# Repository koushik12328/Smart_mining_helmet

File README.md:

# Smart Mining Helmet for Real Time Hazard Detection
**Developed by:** Ch Koushik | MGIT ECE

---

## 1. Aim
To design and develop a decentralized, infrastructure-less safety system for underground mining that utilizes **Machine-to-Machine (M2M)** communication to provide real-time environmental monitoring and instant hazard alerts without relying on Wi-Fi or cellular networks.

## 2. Abstract
Underground mining environments present a unique challenge for safety communication due to signal attenuation through rock strata and the high cost of network infrastructure. This project proposes a **Smart Mining Helmet** that functions as an autonomous node. By leveraging the **ESP-NOW** protocol, the helmet (Transmitter) communicates directly with a base station (Receiver) via hardware MAC addresses. 

The system integrates a multi-sensor array—including Methane (MQ-4), smoke (MQ-2), air quality (MQ-135), and environmental sensors (DHT11, BMP180)—to monitor for life-threatening conditions. Hardware design was executed in **KiCad** for optimized signal integrity, while the software architecture employs a non-blocking state machine with digital filtering to ensure data reliability. Results demonstrate ultra-low latency (<10ms) and robust connectivity, proving the system's efficacy for real-time industrial safety applications.

---

## 3. Components Required

### A. Smart Helmet (Transmitter Module)
* **ESP32 DevKit V1:** Core microcontroller utilizing the ESP-NOW protocol for data broadcast.
* **MQ-4 Sensor:** Dedicated for Methane (CH4) gas detection.
* **MQ-2 Sensor:** Detects Smoke, LPG, and Carbon Monoxide.
* **MQ-135 Sensor:** Monitors general Air Quality (NH3, Benzene, etc.).
* **DHT11:** Provides Temperature and Humidity data.
* **BMP180:** High-precision sensor for Barometric Pressure and Altitude monitoring.
* **Status LEDs:** Local indicators for power and transmission verification.
* **Custom Transmitter PCB:** Designed in KiCad with a compact form factor for helmet mounting.

### B. Base Station / Node (Receiver Module)
* **ESP32 DevKit V1:** Configured to listen for specific MAC addresses and process incoming data packets.
* **16x2 LCD with I2C Module:** Displays real-time sensor telemetry from the helmet.
* **Active Buzzer (5V):** Sounds a high-decibel alarm when sensor thresholds are breached.
* **Visual Alarm LED:** High-intensity LED for immediate hazard recognition.
* **Custom Receiver PCB:** Designed in KiCad with an integrated I2C header and centralized power distribution.

---

## 4. Procedure

### A. Hardware Analysis
The hardware design focuses on **Signal Integrity** and **Power Management**. 
* **Sensing Layer:** The gas sensors (MQ series) are analog; their output is fed into the ESP32’s 12-bit ADC. I implemented a common ground plane in KiCad to reduce noise during high-frequency Wi-Fi bursts.
* **PCB Strategy:** The Transmitter PCB is designed for a compact footprint to fit the helmet. The Receiver PCB utilizes the **I2C protocol** via the PCF8574 expander, which allowed me to reduce the LCD wiring from 10+ pins down to just 2 (SDA/SCL), simplifying the routing significantly.
* **Power Logic:** Because the MQ sensors have internal heaters that pull high current (~800mA peak), I ensured the power traces on the PCB were wide enough to prevent voltage drops that could crash the ESP32.

### B. Software Analysis
The software is the "intelligence" of the system, acting as a non-blocking state machine.
* **M2M Protocol (ESP-NOW):** Unlike standard Wi-Fi, the firmware bypasses the router. I hardcoded the Receiver's hardware MAC address into the Transmitter’s peer list. This allows for near-instant "Power-On-to-Data" transmission.
* **Data Structuring:** I defined a custom `struct` to package sensor values. This ensures that the Receiver interprets the incoming raw bytes correctly every time.
* **Signal Processing:** To handle the inherent "jitter" of analog gas sensors, I implemented a **Moving Average Filter** in the C++ code. This smooths out the readings before they are sent over the air.
* **Callback & ACK:** The software uses the `OnDataSent` callback. If the Receiver is out of range, the code detects the lack of an Acknowledgement (ACK) and triggers a "Link Fail" state without stopping the sensor polling loop.

---

## 5. Implementation
1. **PCB Fabrication:** The KiCad layouts were exported to Gerbers for fabrication.
2. **Firmware Upload:** The TX module was flashed with the sensor-gathering and ESP-NOW broadcast code. The RX module was flashed with the display and alert logic.
3. **M2M Pairing:** MAC addresses were verified and hardcoded for a dedicated point-to-point link.

---

## 6. Observations
* **Latency:** The "Sensor-to-Alert" delay was measured at approximately **10ms**, significantly faster than any Cloud-based IoT setup.
* **I2C Efficiency:** The I2C bus remained stable at 100kHz, providing clean data updates to the LCD every 500ms.
* **Range:** The ESP-NOW link remained robust even through moderate industrial interference, reaching up to 50 meters in non-line-of-sight conditions.

---

## 7. Results
* **Successful M2M Link:** Established a permanent MAC-to-MAC connection that requires zero external network infrastructure.
* **Hazard Response:** The system successfully triggered the buzzer within milliseconds of exposing the MQ-4 sensor to a methane-simulated environment.
* **Data Accuracy:** The moving average filter effectively removed ADC noise, providing stable, reliable PPM readings on the LCD.

---

## 8. Conclusion
The project proves that for high-risk environments like mines, **Machine-to-Machine (M2M)** communication is far superior to standard IoT. By combining custom KiCad hardware with a lean, non-blocking software stack, I created a safety system that is faster, more reliable, and completely independent of the internet.

---
*Department of Electronics and Communication Engineering | MGIT, Hyderabad*

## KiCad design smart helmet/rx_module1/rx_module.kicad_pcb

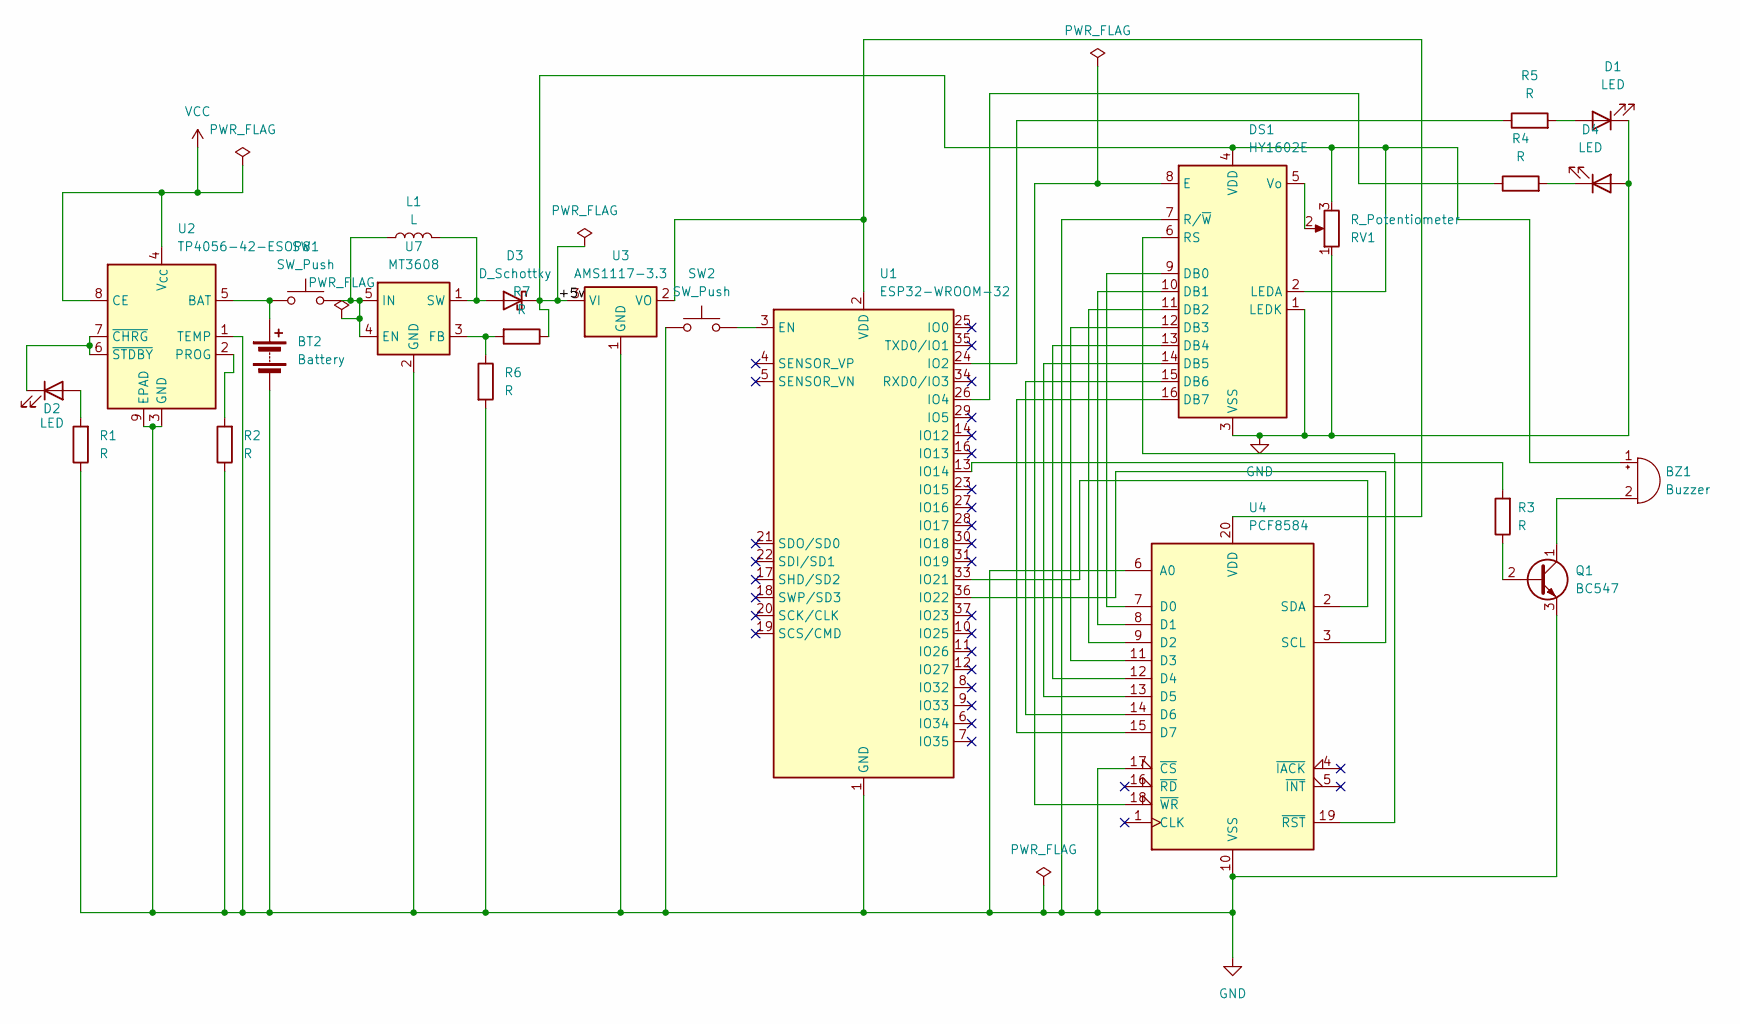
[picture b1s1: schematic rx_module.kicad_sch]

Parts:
BT2: Battery; JST_PH_S2B-PH-K_1x02_P2.00mm_Horizontal
BZ1: Buzzer; Buzzer_12x9.5RM7.6
D1, D2, D4: LED; LED_D5.0mm
D3: D_Schottky; D_SMA
DS1: HY1602E
L1: L; L_Radial_D7.8mm_P5.00mm_Fastron_07HCP
Q1: BC547; TO-92_Inline
R1, R2, R3, R4, R5, R6, R7: R; R_Axial_DIN0207_L6.3mm_D2.5mm_P7.62mm_Horizontal
RV1: R_Potentiometer; Potentiometer_Bourns_3386P_Vertical
SW1, SW2: SW_Push; SW_PUSH_6mm
U1: ESP32-WROOM-32
U2: TP4056-42-ESOP8; SOIC-8-1EP_3.9x4.9mm_P1.27mm_EP2.41x3.3mm_ThermalVias
U3: AMS1117-3.3; SOT-223-3_TabPin2
U4: PCF8584; DIP-20_W7.62mm
U7: MT3608; SOT-23-6

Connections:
/+5v: BZ1.1 (+), D3.1 (K), DS1.2 (LEDA), DS1.4 (VDD), R7.1, RV1.3, U3.3 (VI); also elsewhere on the board
GND: BT2.2 (-), D1.1 (K), D4.2 (A), DS1.1 (LEDK), DS1.3 (VSS), DS1.7 (R/~W), Q1.3 (E), R1.1, R2.1, R6.2, RV1.1, SW2.1, U1.1 (GND), U1.15 (GND), U1.38 (GND), U1.39 (GND), U2.1 (TEMP), U2.3 (GND), U2.9 (EPAD), U3.1 (GND), U4.6 (A0), U4.10 (VSS), U4.17 (~CS), U7.2 (GND); also elsewhere on the board
unnamed: BT2.1 (+), SW1.1, U2.5 (BAT)
unnamed: BZ1.2 (-), Q1.1 (C)
unnamed: D1.2 (A), R5.2
unnamed: D2.2 (A), R1.2
unnamed: D2.1 (K), U2.6 (~STDBY), U2.7 (~CHRG)
unnamed: D3.2 (A), L1.2, U7.1 (SW)
unnamed: D4.1 (K), R4.2
unnamed: DS1.9 (DB0), U4.7 (D0)
unnamed: DS1.10 (DB1), U4.8 (D1)
unnamed: DS1.11 (DB2), U4.9 (D2)
unnamed: DS1.12 (DB3), U4.11 (D3)
unnamed: DS1.13 (DB4), U4.12 (D4)
unnamed: DS1.14 (DB5), U4.13 (D5)
unnamed: DS1.15 (DB6), U4.14 (D6)
unnamed: DS1.16 (DB7), U4.15 (D7)
unnamed: DS1.8 (E), U4.18 (~WR)
unnamed: DS1.6 (RS), U4.19 (~RST)
unnamed: DS1.5 (Vo), RV1.2
unnamed: Q1.2 (B), R3.1
unnamed: SW2.2, U1.3 (EN)
unnamed: R5.1, U1.24 (IO2)
unnamed: R4.1, U1.26 (IO4)
unnamed: R3.2, U1.13 (IO14)
unnamed: U1.33 (IO21), U4.2 (SDA)
unnamed: U1.36 (IO22), U4.3 (SCL)
unnamed 27: U1.2 (VDD), U3.2 (VO), U4.20 (VDD); also elsewhere on the board
unnamed: R2.2, U2.2 (PROG)
unnamed: L1.1, SW1.2, U7.4 (EN), U7.5 (IN)
unnamed: R6.1, R7.2, U7.3 (FB)
VCC: U2.4 (V_{CC}), U2.8 (CE)

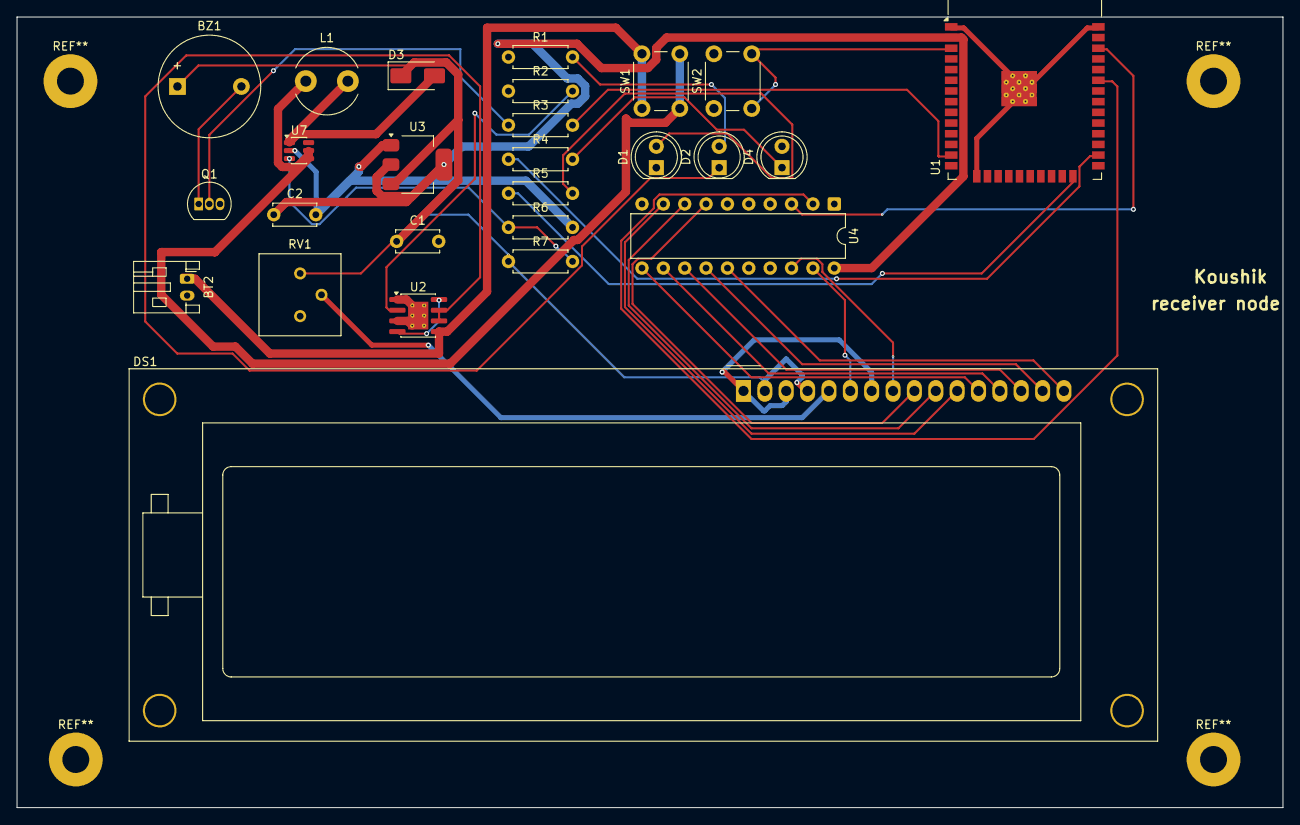
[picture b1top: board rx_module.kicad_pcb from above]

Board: 2 copper layers, 150.5 x 94.0 mm, 26 parts (0 on the bottom side), 32 nets.

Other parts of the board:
C1, C2: C; C_Disc_D5.0mm_W2.5mm_P5.00mm

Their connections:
/+5v: C1.1; also elsewhere on the board
GND: C1.2, C2.2; also elsewhere on the board
unnamed 27: C2.1; also elsewhere on the board

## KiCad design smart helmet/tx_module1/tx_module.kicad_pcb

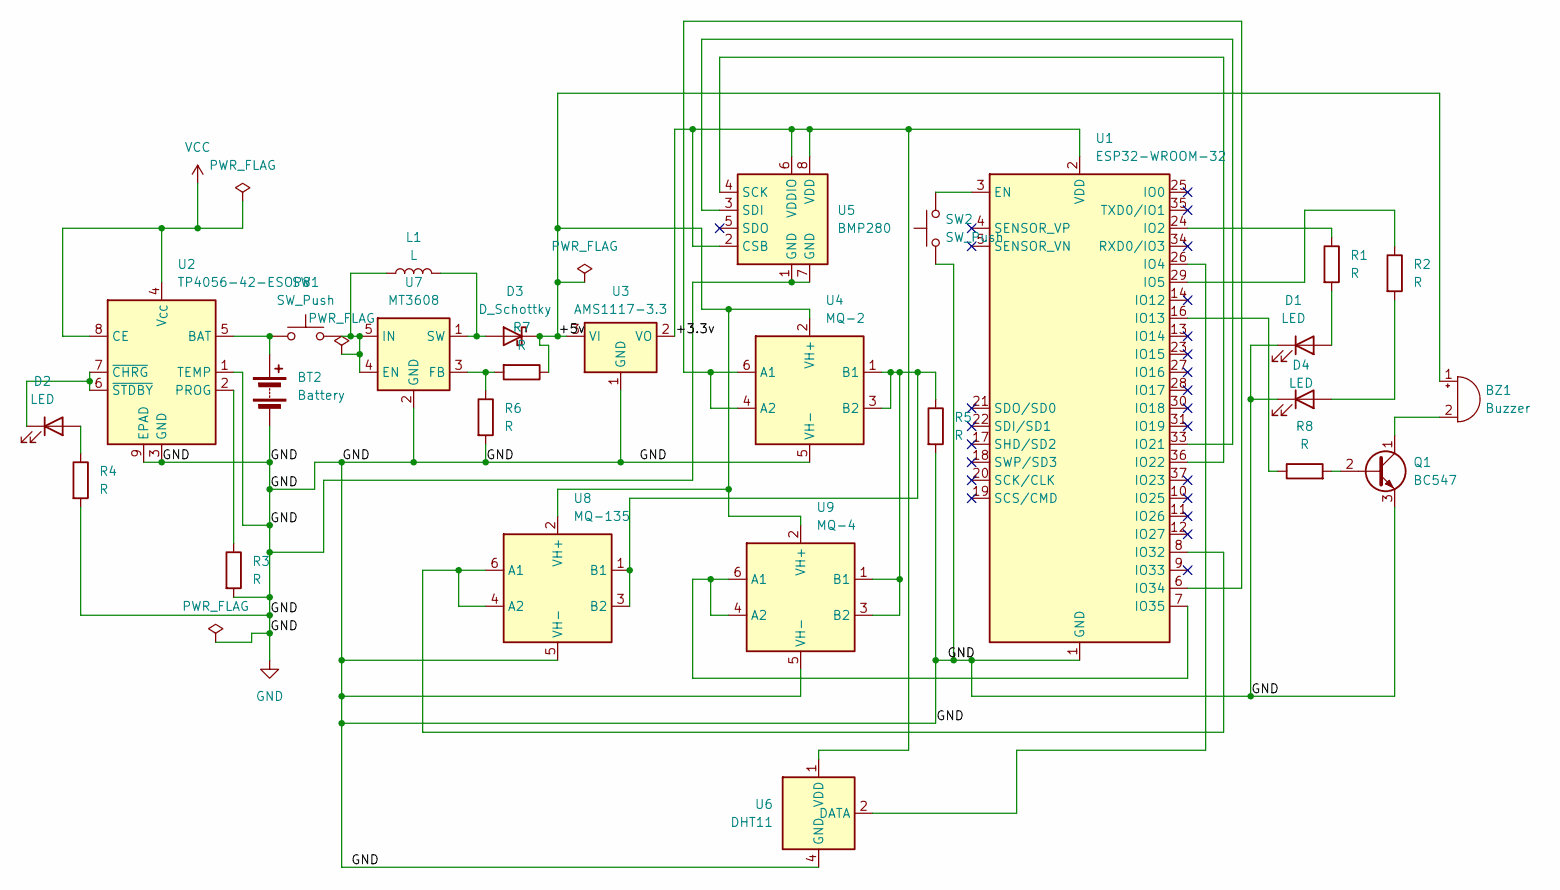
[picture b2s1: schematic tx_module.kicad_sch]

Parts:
BT2: Battery; JST_PH_S2B-PH-K_1x02_P2.00mm_Horizontal
BZ1: Buzzer; Buzzer_12x9.5RM7.6
D1, D2, D4: LED; LED_D5.0mm
D3: D_Schottky; D_SMA
L1: L; L_Radial_D7.8mm_P5.00mm_Fastron_07HCP
Q1: BC547; TO-92_Inline
R1, R2, R3, R4, R5, R6, R7, R8: R; R_Axial_DIN0207_L6.3mm_D2.5mm_P7.62mm_Horizontal
SW1, SW2: SW_Push; L_APV_ANR5012
U1: ESP32-WROOM-32
U2: TP4056-42-ESOP8; SOIC-8-1EP_3.9x4.9mm_P1.27mm_EP2.41x3.3mm_ThermalVias
U3: AMS1117-3.3; SOT-223-3_TabPin2
U4: MQ-2; MQ-6
U5: BMP280; Bosch_LGA-8_2x2.5mm_P0.65mm_ClockwisePinNumbering
U6: DHT11; Aosong_DHT11_5.5x12.0_P2.54mm
U7: MT3608; SOT-23-6
U8: MQ-135; MQ-6
U9: MQ-4; MQ-6

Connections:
/+3.3v: U1.2 (VDD), U3.2 (VO), U5.2 (CSB), U5.6 (VDDIO), U5.8 (VDD), U6.1 (VDD)
/+5v: BZ1.1 (+), D3.1 (K), R7.1, U3.3 (VI), U4.2 (VH+), U8.2 (VH+), U9.2 (VH+)
GND: BT2.2 (-), D1.1 (K), D4.1 (K), Q1.3 (E), R3.2, R4.2, R5.2, R6.2, SW2.1, U1.1 (GND), U1.15 (GND), U1.38 (GND), U1.39 (GND), U2.1 (TEMP), U2.3 (GND), U2.9 (EPAD), U3.1 (GND), U4.5 (VH-), U5.1 (GND), U5.7 (GND), U6.4 (GND), U7.2 (GND), U8.5 (VH-), U9.5 (VH-)
unnamed: BT2.1 (+), SW1.1, U2.5 (BAT)
unnamed: BZ1.2 (-), Q1.1 (C)
unnamed: D1.2 (A), R1.2
unnamed: D2.2 (A), R4.1
unnamed: D2.1 (K), U2.6 (~STDBY), U2.7 (~CHRG)
unnamed: D3.2 (A), L1.2, U7.1 (SW)
unnamed: D4.2 (A), R2.2
unnamed: Q1.2 (B), R8.2
unnamed: SW2.2, U1.3 (EN)
unnamed: R1.1, U1.24 (IO2)
unnamed: U1.26 (IO4), U6.2 (DATA)
unnamed: R2.1, U1.29 (IO5)
unnamed: R8.1, U1.16 (IO13)
unnamed: U1.33 (IO21), U5.3 (SDI)
unnamed: U1.36 (IO22), U5.4 (SCK)
unnamed: U1.8 (IO32), U8.4 (A2), U8.6 (A1)
unnamed: U1.6 (IO34), U4.4 (A2), U4.6 (A1)
unnamed: U1.7 (IO35), U9.4 (A2), U9.6 (A1)
unnamed: R3.1, U2.2 (PROG)
unnamed: R5.1, U4.1 (B1), U4.3 (B2), U8.1 (B1), U8.3 (B2), U9.1 (B1), U9.3 (B2)
unnamed: L1.1, SW1.2, U7.4 (EN), U7.5 (IN)
unnamed: R6.1, R7.2, U7.3 (FB)
VCC: U2.4 (V_{CC}), U2.8 (CE)

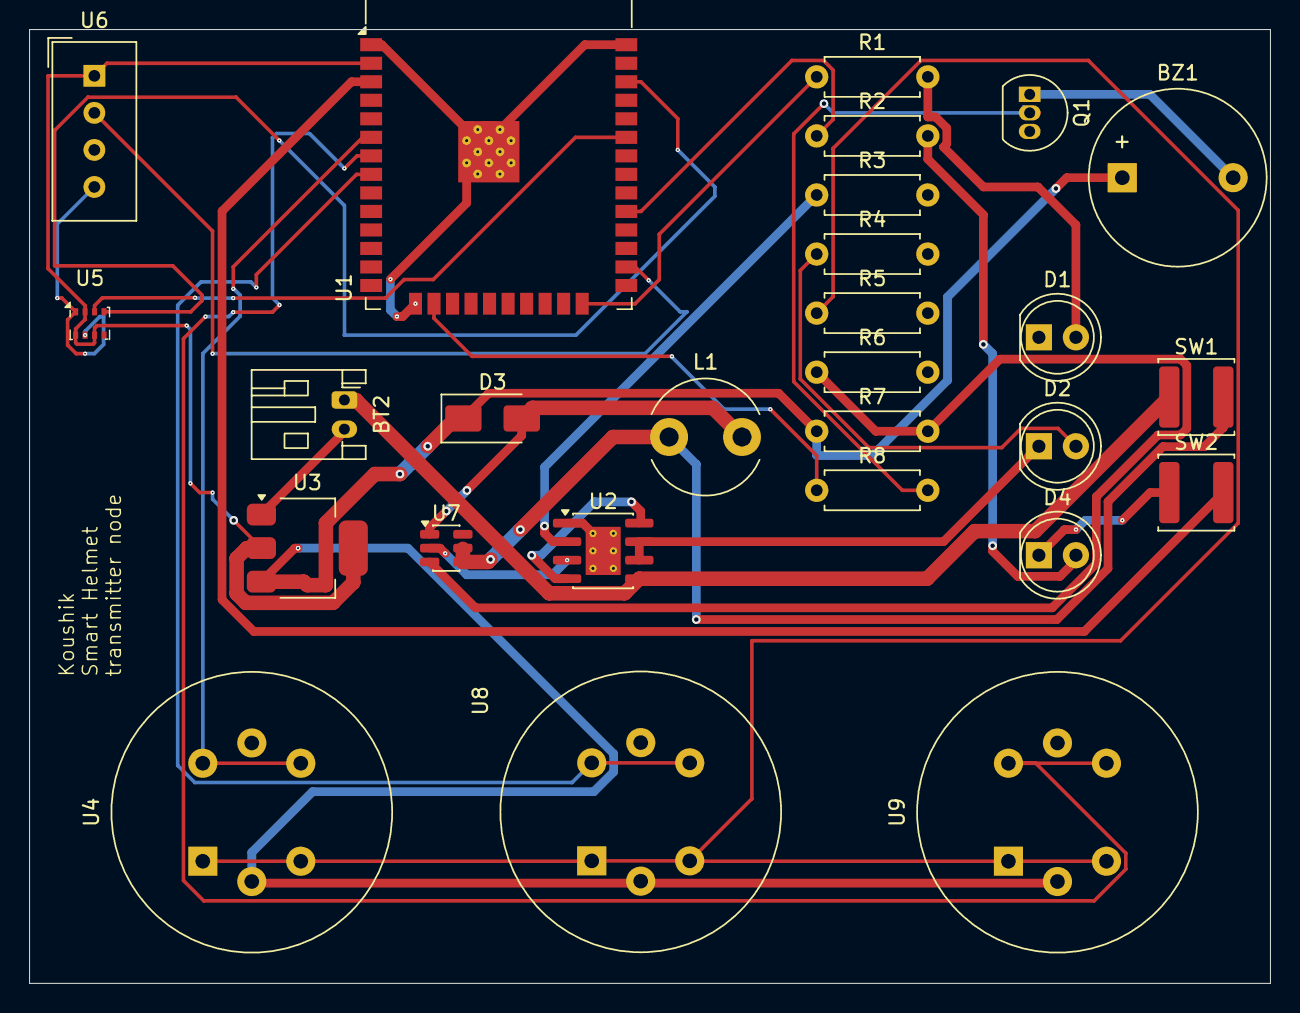
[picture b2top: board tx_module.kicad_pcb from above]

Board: 2 copper layers, 85.1 x 65.4 mm, 27 parts (0 on the bottom side), 26 nets.

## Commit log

2026-05-04 Initial upload of helmet project
    An ESP32-based safety helmet system featuring real-time gas detection, impact/tilt sensing, and localized alerts for hazardous environments.
2026-05-04 Revise README with project overview and details
    Expanded project details, methodology, and implementation status for the Smart Mining Helmet.
2026-05-04 Initial README.md for Smart Mining Helmet project
    Added detailed project description, methodology, experimental results, and references for the Smart Mining Helmet project.
2026-05-07 Add initial PCB layouts for TX and RX modules
    Initial routing and component placement for the transmitter (TX) and receiver (RX) modules.
    Defined board constraints, layer stackup (2-layer), and edge cuts.
    Includes footprint assignments for the ESP32, sensors, and I2C LCD interface.
2026-05-07 Add README for Smart Mining Helmet project
    Added detailed project overview, components, procedures, and results for the Smart Mining Helmet system.
